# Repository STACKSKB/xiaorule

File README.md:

# xiaorule
A Seeeduino Xiao based functional FR4 ruler.

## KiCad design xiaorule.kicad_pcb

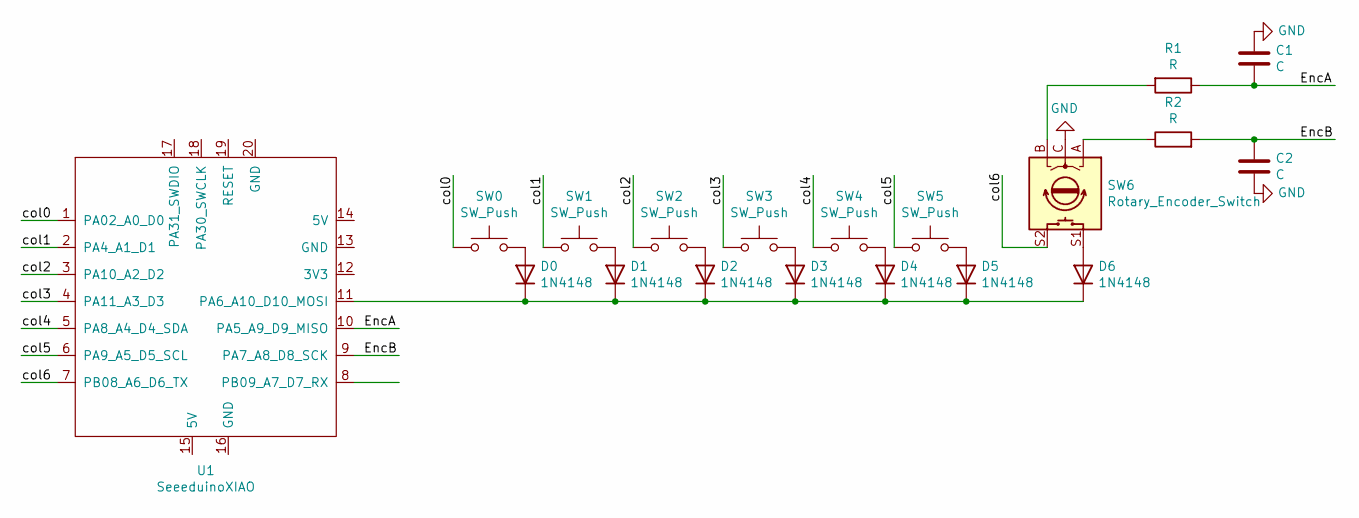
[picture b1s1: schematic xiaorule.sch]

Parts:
C1, C2: C; C_0603_1608Metric_Pad1.08x0.95mm_HandSolder
D0, D1, D2, D3, D4, D5, D6: 1N4148; D3_SMD
R1, R2: R; R_0603_1608Metric_Pad0.98x0.95mm_HandSolder
SW0, SW1, SW2, SW3, SW4, SW5: SW_Push; Kailh_socket_MX_optional
SW6: Rotary_Encoder_Switch; RotaryEncoder_Alps_EC11E-Switch_Vertical_H20mm
U1: SeeeduinoXIAO; Seeeduino XIAO-MOUDLE14P-2.54-21X17.8MM

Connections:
/EncA: C1.2, R1.1, U1.10 (PA5_A9_D9_MISO)
/EncB: C2.1, R2.2, U1.9 (PA7_A8_D8_SCK)
/col0: SW0.1, U1.1 (PA02_A0_D0)
/col1: SW1.1, U1.2 (PA4_A1_D1)
/col2: SW2.1, U1.3 (PA10_A2_D2)
/col3: SW3.1, U1.4 (PA11_A3_D3)
/col4: SW4.1, U1.5 (PA8_A4_D4_SDA)
/col5: SW5.1, U1.6 (PA9_A5_D5_SCL)
/col6: SW6.S2, U1.7 (PB08_A6_D6_TX)
GND: C1.1, C2.2, SW6.C
unnamed: D0.1 (K), D1.1 (K), D2.1 (K), D3.1 (K), D4.1 (K), D5.1 (K), D6.1 (K), U1.11 (PA6_A10_D10_MOSI)
unnamed: D0.2 (A), SW0.2
unnamed: D1.2 (A), SW1.2
unnamed: D2.2 (A), SW2.2
unnamed: D3.2 (A), SW3.2
unnamed: D4.2 (A), SW4.2
unnamed: D5.2 (A), SW5.2
unnamed: D6.2 (A), SW6.S1
unnamed: R1.2, SW6.B
unnamed: R2.1, SW6.A

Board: 2 copper layers, 19 parts (0 on the bottom side), 20 nets, no tracks yet.

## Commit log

2021-07-07 Schematic
2021-08-28 rotary enc
2021-08-28 add keyswitchs submodule
2021-08-29 dump everything into circuit board
2021-08-30 start laying out pcb
2021-08-30 remove sw5
